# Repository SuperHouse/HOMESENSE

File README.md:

HomeSense Basic Environmental Sensor
====================================
Copyright 2018-2019 SuperHouse Pty Ltd  www.superhouse.tv  

Environmental sensor for home automation systems. Includes:

 * ESP8266 processor with WiFi
 * Switchmode voltage regulator for wide input voltage range
 * BME280 barometric pressure, temperature, and humidity sensor
 * I2C breakout with prototyping area
 * Designed to run Tasmota firmware

More information at

  http://www.superhouse.tv/hsbasic

INSTALLATION
------------
The design is saved as an EAGLE project. EAGLE PCB design software is
available from www.cadsoftusa.com free for non-commercial use. To use
this project download it and place the directory containing these files
into the "eagle" directory on your computer. Then open EAGLE and
navigate to the project.

DISTRIBUTION
------------
The specific terms of distribution of this project are governed by the
license referenced below.

LICENSE
-------
Licensed under the TAPR Open Hardware License (www.tapr.org/OHL).
The "license" folder within this repository also contains a copy of
this license in plain text format.

CREDIT
-------
Designed by Jonathan Oxer

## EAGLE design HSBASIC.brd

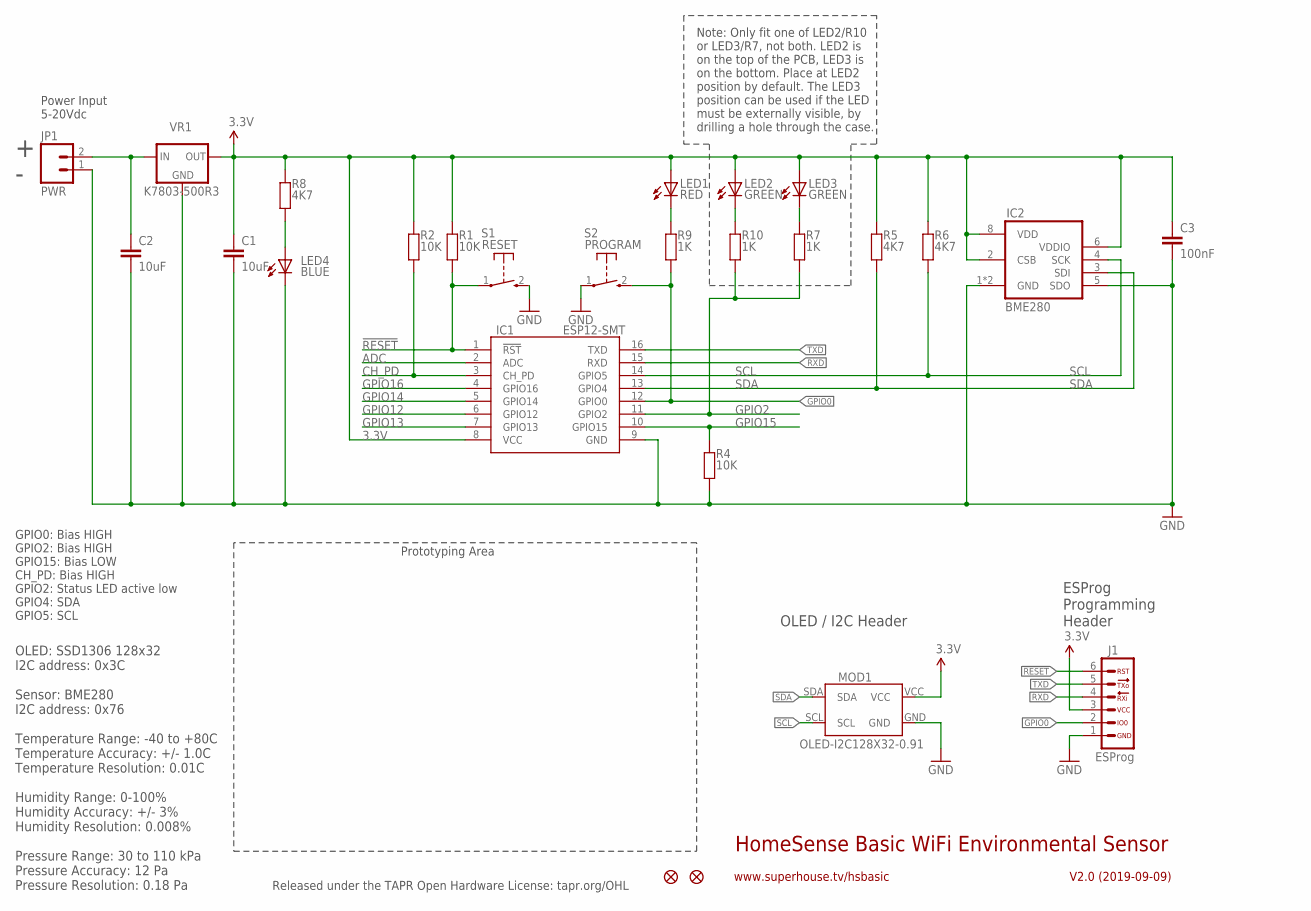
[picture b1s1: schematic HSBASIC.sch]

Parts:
C1, C2: 10uF; C0805
C3: 100nF; C0603
FID2, FID3: FIDUCIAL1X2.5; FIDUCIAL-1X2.5
IC1: ESP12-SMT; ESP12
IC2: BME280
J1: ESPROG-SOCKET; ESPROG-S
JP1: PWR; 1X02
LED1: RED; LED-0603
LED2, LED3: GREEN; LED-0603
LED4: BLUE; LED-0603
MOD1: OLED-I2C128X32-0.91; OLED-128X32-0.91
R1, R2, R4: 10K; R0603
R5, R6, R8: 4K7; R0603
R7, R9, R10: 1K; R0603
S1: RESET; TACTILE_SMT_3X4X2
S2: PROGRAM; TACTILE_SMT_3X4X2
VR1: K7803-500R3; K78XX-500R3-FLAT

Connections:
3.3V: C1.1, C3.1, IC1.8 (VCC), IC2.2 (CSB), IC2.6 (VDDIO), IC2.8 (VDD), J1.3, LED1.A, LED2.A, LED3.A, MOD1.VCC, R1.2, R2.2, R5.2, R6.2, R8.2, VR1.3 (OUT)
!RESET: IC1.1 (!RST), J1.6, R1.1, S1.1
ADC: IC1.2 (ADC)
CH_PD: IC1.3 (CH_PD), R2.1
GND: C1.2, C2.2, C3.2, IC1.9 (GND), IC2.1 (GND), IC2.5 (SDO), IC2.7 (GND), J1.1, JP1.1, LED4.C, MOD1.GND, R4.1, S1.2 (S), S2.1, VR1.2 (GND)
GPIO0: IC1.12 (GPIO0), J1.2, R9.1, S2.2 (S)
GPIO2: IC1.11 (GPIO2), R7.1, R10.1
GPIO12: IC1.6 (GPIO12)
GPIO13: IC1.7 (GPIO13)
GPIO14: IC1.5 (GPIO14)
GPIO15: IC1.10 (GPIO15), R4.2
GPIO16: IC1.4 (GPIO16)
unnamed: C2.1, JP1.2, VR1.1 (IN)
unnamed: LED4.A, R8.1
unnamed: LED1.C, R9.2
unnamed: LED3.C, R7.2
unnamed: LED2.C, R10.2
RXD: IC1.15 (RXD), J1.4
SCL: IC1.14 (GPIO5), IC2.4 (SCK), MOD1.SCL, R6.1
SDA: IC1.13 (GPIO4), IC2.3 (SDI), MOD1.SDA, R5.1
TXD: IC1.16 (TXD), J1.5

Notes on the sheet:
HomeSense Basic WiFi Environmental Sensor
V2.0 (2019-09-09)
www.superhouse.tv/hsbasic
Released under the TAPR Open Hardware License: tapr.org/OHL
GPIO0: Bias HIGH GPIO2: Bias HIGH GPIO15: Bias LOW CH_PD: Bias HIGH GPIO2: Status LED active low GPIO4: SDA GPIO5: SCL
OLED: SSD1306 128x32 I2C address: 0x3C Sensor: BME280 I2C address: 0x76 Temperature Range: -40 to +80C Temperature Accuracy: +/- 1.0C Temperature Resolution: 0.01C Humidity Range: 0-100% Humidity Accuracy: +/- 3% Humidity Resolution: 0.008% Pressure Range: 30 to 110 kPa Pressure Accuracy: 12 Pa Pre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
Power Input 5-20Vdc
Note: Only fit one of LED2/R10 or LED3/R7, not both. LED2 is on the top of the PCB, LED3 is on the bottom. Place at LED2 position by default. The LED3 position can be used if the LED must be externally visible, by drilling a hole through the case.
ESProg Programming Header
Prototyping Area
OLED / I2C Header

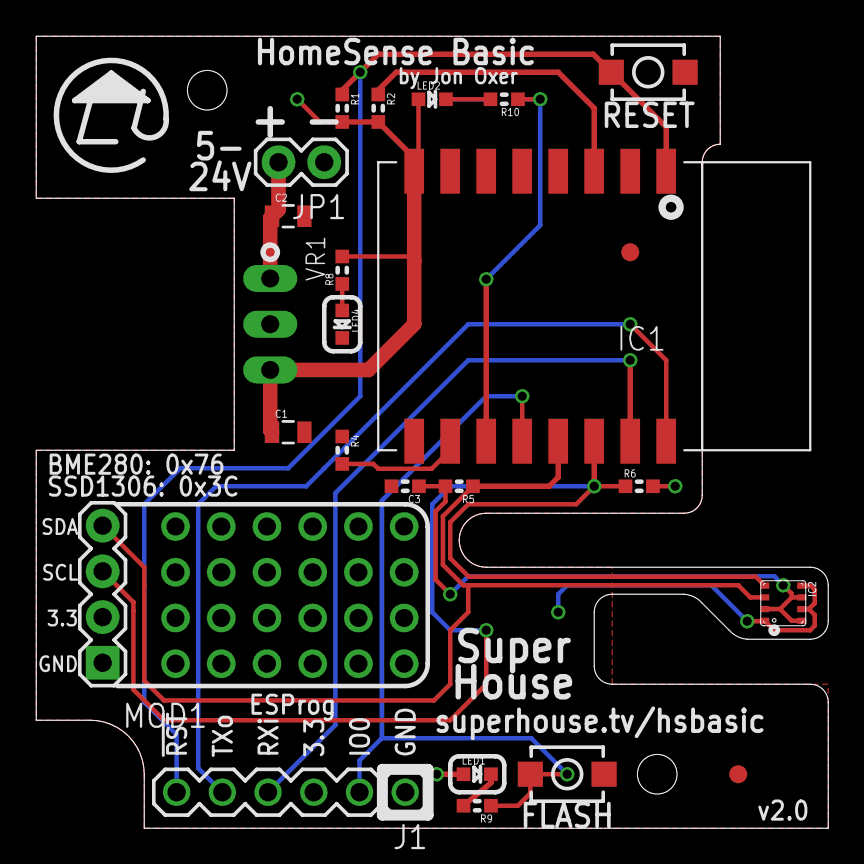
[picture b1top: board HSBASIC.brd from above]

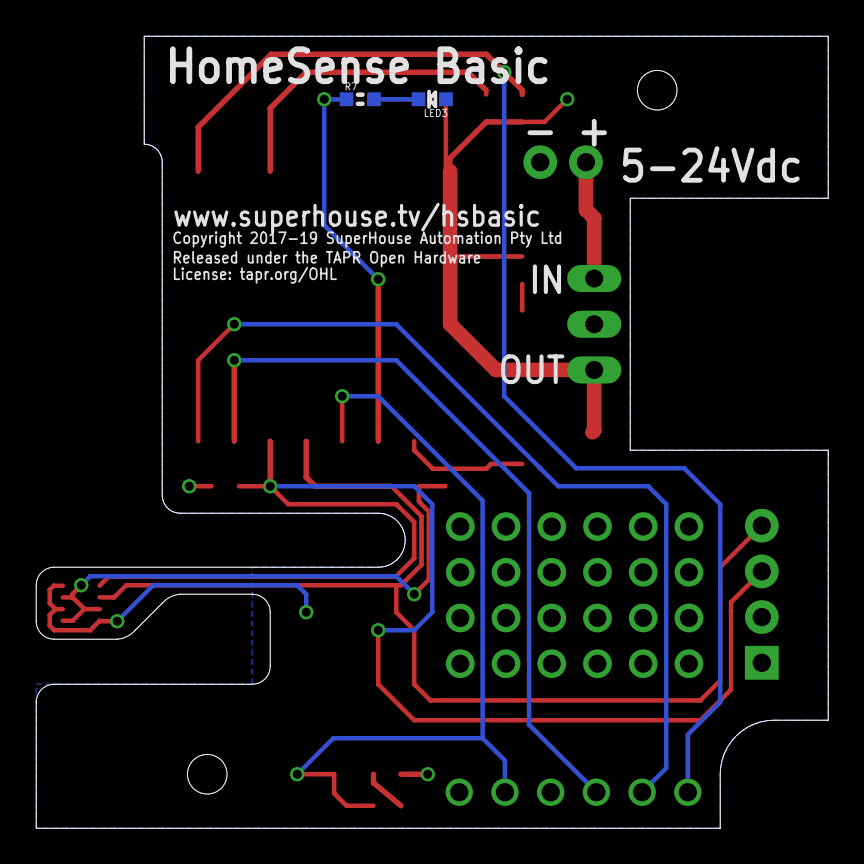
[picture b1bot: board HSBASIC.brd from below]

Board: 2 copper layers, 44.0 x 44.0 mm, 26 parts (2 on the bottom side), 16 nets.

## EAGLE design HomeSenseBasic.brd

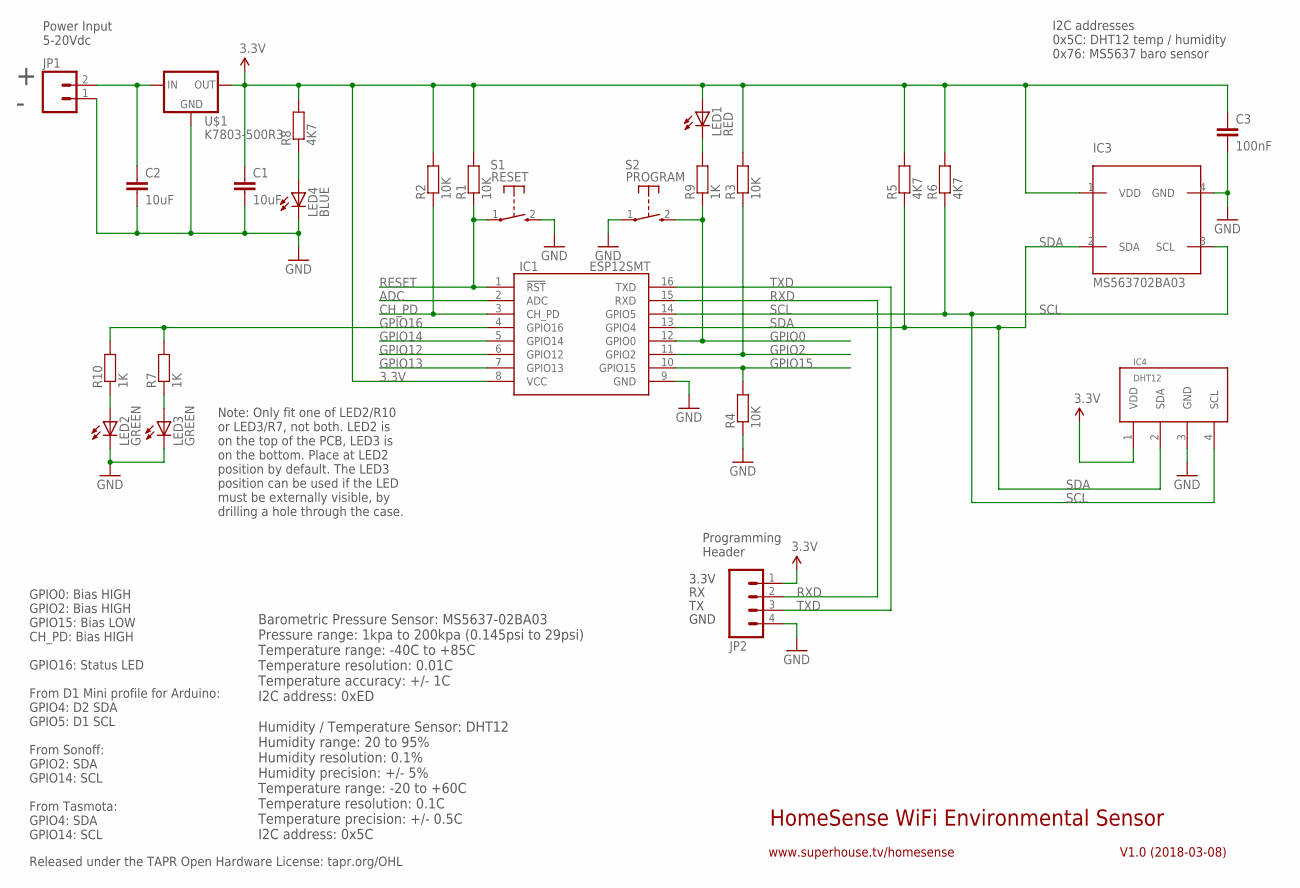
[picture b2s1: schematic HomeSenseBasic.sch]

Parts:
C1, C2: 10uF; 0805
C3: 100nF; 0603
IC1: ESP12SMT; ESP12
IC3: MS563702BA03; MS5637
IC4: DHT12
JP1: M02PTH; 1X02
JP2: M04PTH; 1X04
LED1: RED; LED-0603
LED2, LED3: GREEN; LED-0603
LED4: BLUE; LED-0603
R1, R2, R3, R4: 10K; 0603
R5, R6, R8: 4K7; 0603
R7, R9, R10: 1K; 0603
S1: RESET; TACTILE_SWITCH_SMD_2PIN_TINY
S2: PROGRAM; TACTILE_SWITCH_SMD_2PIN_TINY
U$1: K7803-500R3; K78XX-500R3

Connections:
3.3V: C1.1, C3.1, IC1.8 (VCC), IC3.1 (VDD), IC4.1 (VDD), JP2.1, LED1.A, R1.2, R2.2, R3.2, R5.2, R6.2, R8.2, U$1.3 (OUT)
ADC: IC1.2 (ADC)
CH_PD: IC1.3 (CH_PD), R2.1
GND: C1.2, C2.2, C3.2, IC1.9 (GND), IC3.4 (GND), IC4.3 (GND), JP1.1, JP2.4, LED2.C, LED3.C, LED4.C, R4.1, S1.2 (S), S2.1, U$1.2 (GND)
GPIO0: IC1.12 (GPIO0), R9.1, S2.2 (S)
GPIO2: IC1.11 (GPIO2), R3.1
GPIO12: IC1.6 (GPIO12)
GPIO13: IC1.7 (GPIO13)
GPIO14: IC1.5 (GPIO14)
GPIO15: IC1.10 (GPIO15), R4.2
GPIO16: IC1.4 (GPIO16), R7.2, R10.2
unnamed: C2.1, JP1.2, U$1.1 (IN)
unnamed: LED4.A, R8.1
unnamed: LED1.C, R9.2
unnamed: LED2.A, R10.1
unnamed: LED3.A, R7.1
RESET: IC1.1 (!RST), R1.1, S1.1
RXD: IC1.15 (RXD), JP2.2
SCL: IC1.14 (GPIO5), IC3.3 (SCL), IC4.4 (SCL), R6.1
SDA: IC1.13 (GPIO4), IC3.2 (SDA), IC4.2 (SDA), R5.1
TXD: IC1.16 (TXD), JP2.3

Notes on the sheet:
HomeSense WiFi Environmental Sensor
V1.0 (2018-03-08)
www.superhouse.tv/homesense
Released under the TAPR Open Hardware License: tapr.org/OHL
GPIO0: Bias HIGH GPIO2: Bias HIGH GPIO15: Bias LOW CH_PD: Bias HIGH GPIO16: Status LED From D1 Mini profile for Arduino: GPIO4: D2 SDA GPIO5: D1 SCL From Sonoff: GPIO2: SDA GPIO14: SCL From Tasmota: GPIO4: SDA GPIO14: SCL
I2C addresses 0x5C: DHT12 temp / humidity 0x76: MS5637 baro sensor
Barometric Pressure Sensor: MS5637-02BA03 Pressure range: 1kpa to 200kpa (0.145psi to 29psi) Temperature range: -40C to +85C Temperature resolution: 0.01C Temperature accuracy: +/- 1C I2C address: 0xED Humidity / Temperature Sensor: DHT12 Humidity range: 20 to 95% Humidity resolution: 0.1% Humidity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
3.3V
GND
Power Input 5-20Vdc
Note: Only fit one of LED2/R10 or LED3/R7, not both. LED2 is on the top of the PCB, LED3 is on the bottom. Place at LED2 position by default. The LED3 position can be used if the LED must be externally visible, by drilling a hole through the case.
Programming Header

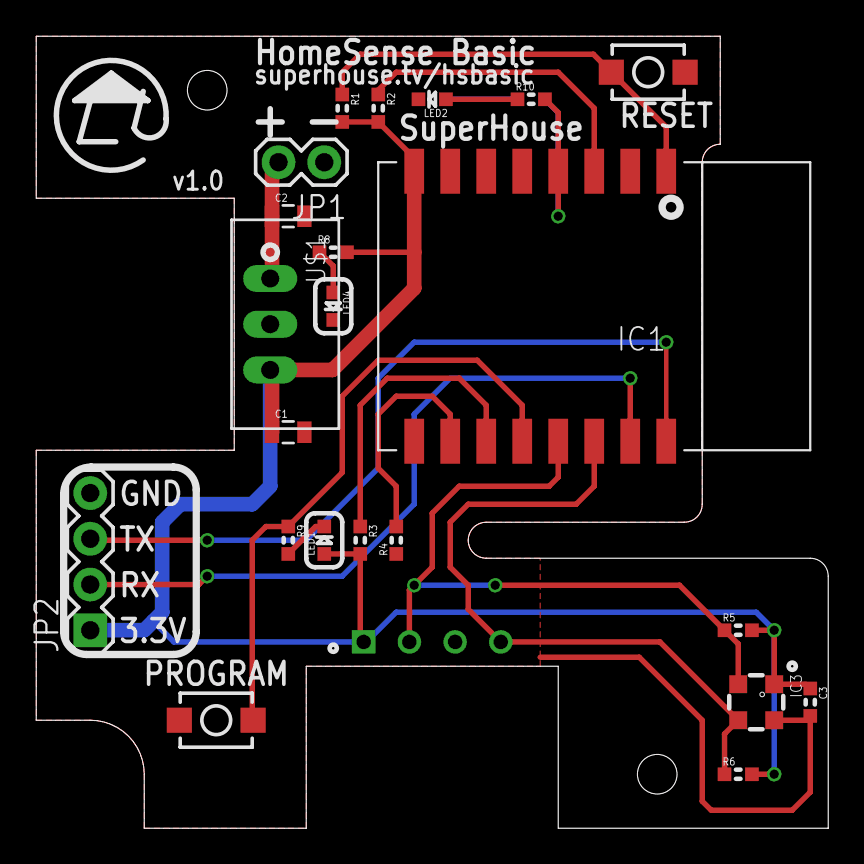
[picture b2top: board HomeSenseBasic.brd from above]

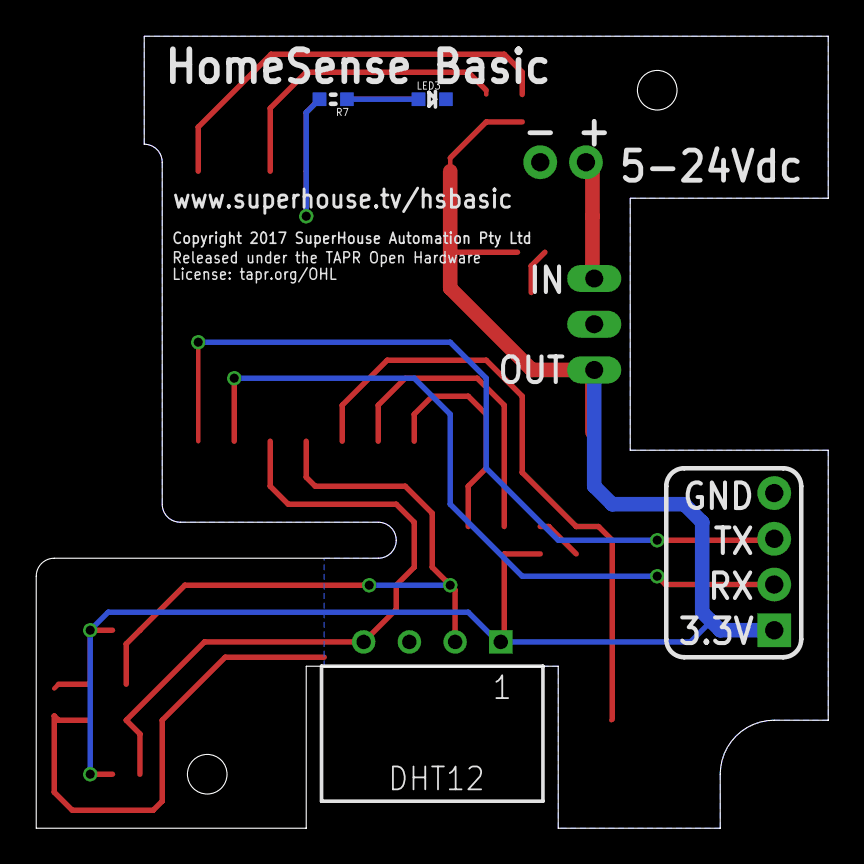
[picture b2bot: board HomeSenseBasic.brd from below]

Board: 2 copper layers, 44.0 x 44.0 mm, 25 parts (3 on the bottom side), 17 nets.

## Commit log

2018-02-14 Initial project import
2018-03-08 Updated routing and schematic for v1.0 release
2018-03-28 Fixed ESP12 footprint with correct GPIO4/5
2018-03-28 Added license files and updated README
2018-03-28 Renamed project files
2019-04-24 Routing
2019-09-03 Switch to BME280 sensor for Tasmota compatibility
2019-09-03 Routing progress
2019-09-07 Routing I2C
2019-09-08 Hopefully final routing for v2.0 release
2019-09-08 Corrected README and added image
2019-09-09 Major restructure to add OLED and prototyping area
2019-09-13 Final tweaks plus ERC and DRC for v2.0 release

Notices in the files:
HSBASIC.brd:
Copyright 2017-19 SuperHouse Automation Pty Ltd
HomeSenseBasic.brd:
Copyright 2017 SuperHouse Automation Pty Ltd
parts and their libraries:
freetronics-original: Licensing: CC v3.0 Share-Alike You are welcome to use this library for commercial purposes.
